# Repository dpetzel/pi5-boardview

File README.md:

# Raspberry Pi 5 board reconstruction

A KiCad 10 reconstruction of the Raspberry Pi 5 board (part placement, part identification, nets traced from the
real board), published as an interactive boardview for repair work.

> [!WARNING]
> **Unofficial, incomplete and possibly wrong.**
> * **Not official.** Not made, endorsed or checked by Raspberry Pi Ltd, and not based on official schematics or layout
>   files. "Raspberry Pi" is a trademark of Raspberry Pi Ltd; this project is not affiliated with it.
> * **Made by a hobbyist.** Reverse engineered by an untrained hobbyist from photos and multimeter probing, not by an
>   electronics professional.
> * **Incomplete and possibly wrong.** Many parts are unidentified and most nets are untraced. Positions, values, part
>   numbers and connections may be wrong, and your board revision may differ.
> * **Use at your own risk.** Board-level repair can destroy hardware and can be dangerous. Check everything against
>   your own board, your own measurements and the manufacturers' datasheets before you solder or apply power. Provided
>   "as is" with no warranty of any kind; the authors and contributors accept no liability for any damage or injury.

* **View it:** <https://dpetzel.github.io/pi5-boardview/>, rebuilt from `main` on every push
* **Download:** [`pi5-boardview.html`](https://dpetzel.github.io/pi5-boardview/pi5-boardview.html) (self-contained,
  works offline) and [`pi5.brd`](https://dpetzel.github.io/pi5-boardview/pi5.brd) (for
  [OpenBoardView](https://github.com/OpenBoardView/OpenBoardView)), always the latest build

## Repository

| Path | What |
|---|---|
| `pi5.kicad_pcb`, `pi5.kicad_pro` | The board. Top and bottom photos are embedded as reference images (Eco1.User = top, Eco2.User = bottom) |
| `pi5.pretty/`, `DA9091.pretty/` | Project footprints |
| `pi5_board_top.png`, `pi5_board_bottom.png` | The source photos embedded in the board |
| `tools/boardview.py`, `tools/template.html` | Exporter (HTML viewer + `.brd`) and the viewer it fills in |
| `.github/workflows/boardview.yml` | CI: builds the boardview and deploys it to Pages |

The boardview files are build output and not committed.

## Contributing

Edit the board in KiCad 10 and open a pull request. Part details go in footprint fields: `Function`, `Part`, `Notes`,
`Replacement`, and `Source` (`Source2`, `Source3`, … for more links). Fields holding a URL show as links in the
viewer. References ending in `**` or `?` (`REF**`, `R?`) are shown as unidentified parts.

Every pull request builds the boardview. Download the `boardview` artifact from the PR's workflow run to check
your change before it's merged.

### Building locally

The exporter needs KiCad's `pcbnew` Python module. With Docker:

```sh
docker run --rm -v "$PWD":/w -w /w kicad/kicad:10.0 python3 tools/boardview.py pi5.kicad_pcb
```

or with the Python bundled with KiCad (on Windows, `"C:\Program Files\KiCad\10.0\bin\python.exe"`):

```sh
python3 tools/boardview.py pi5.kicad_pcb
```

Both write `boardview/pi5-boardview.html` and `boardview/pi5.brd`. Options: `-o DIR`, `--no-photo`,
`--kicad-nets-only` (skip nets derived from copper; see the notes at the top of `tools/boardview.py`).
KiCad exports the last *saved* board, so save before building.

## Credits

The DA9091 PMIC footprint (`DA9091.pretty`, U5) uses the pad geometry from
[schlae/cm5-reveng](https://github.com/schlae/cm5-reveng), a reverse-engineered Raspberry Pi Compute Module 5,
licensed [CC BY-SA 4.0](https://creativecommons.org/licenses/by-sa/4.0/). Its pad numbers are left blank here on
purpose: the DA9091 has no public datasheet to confirm where pin 1 is.

## License

[CC-BY-SA-4.0](LICENSE): share and adapt with attribution, and publish adaptations under the same license.
The license's disclaimer of warranties and limitation of liability apply in full.

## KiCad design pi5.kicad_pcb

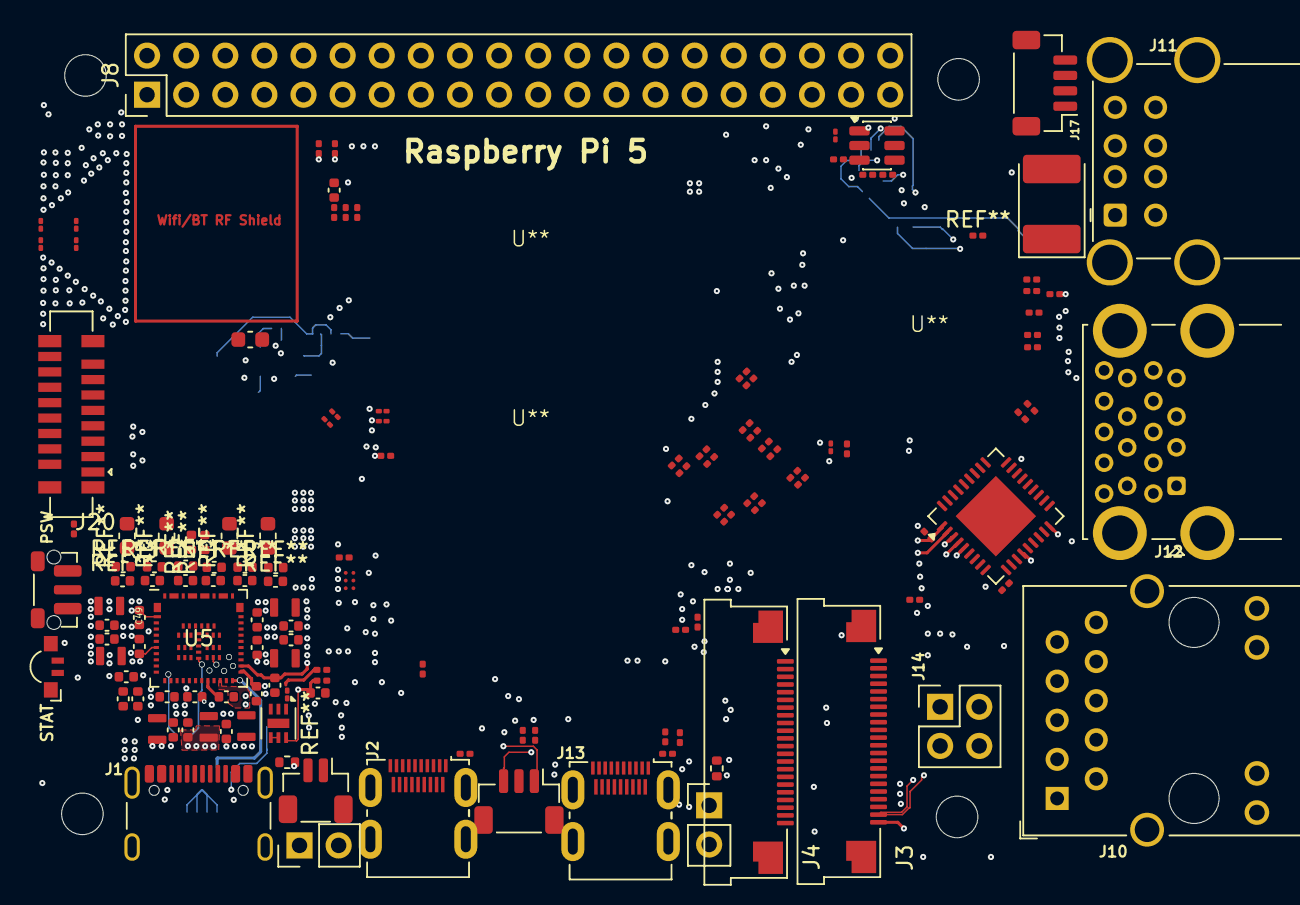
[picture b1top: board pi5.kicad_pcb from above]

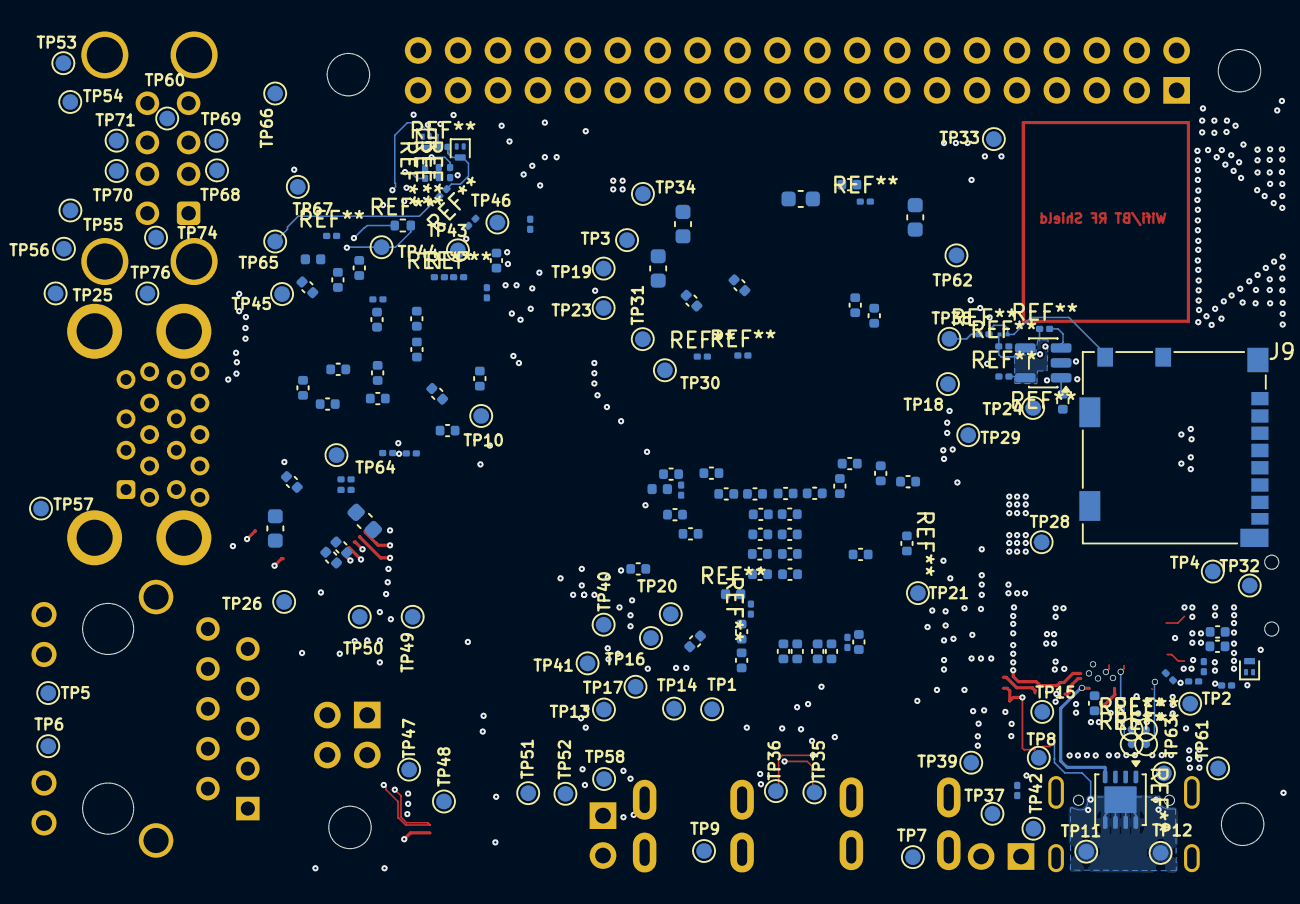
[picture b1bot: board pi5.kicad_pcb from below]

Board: 2 copper layers, 98 parts (78 on the bottom side), 4 nets.

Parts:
C49, C50: 22uF; C_0402_1005Metric
C234: 22uF; C_0603_1608Metric
C263: 4u7; C_0402_1005Metric
J1: USB_C_Receptacle_GCT_USB4105-xx-A_16P_TopMnt_Hori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; USB_C_Receptacle_GCT_USB4105-xx-A_16P_TopMnt_Horizontal
J2, J13: HDMI_Micro-D_Molex_46765-1xxx
J3, J4: F32Q-1A7H1-11022; Amphenol_F32Q-1A7x1-11022_1x22-1MP_P0.5mm_Horizontal
J8: PinHeader_2x20_P2.54mm_Vertical
J9: 104031-0811; microSD_HC_Molex_104031-0811
J10: RJ45_Wuerth_7499111446_Horizontal
J11: USB_A_Wuerth_61400826021_Horizontal_Stacked
J12: USB3_A_Molex_48406-0001_Horizontal_Stacked
J14: PinHeader_2x02_P2.54mm_Vertical
J17: JST_SH_BM04B-SRSS-TB_1x04-1MP_P1.00mm_Vertical
J20: 52559-1652; Molex_52559-1652_2x8-1MP_P0.5mm_Vertical
PSW: SW_Push_1P1T-MP_NO_Horizontal_Alps_SKRTLAE010
R15, R17: 470 Ω; R_0201_0603Metric
R46, R47: 2K Ω; R_0201_0603Metric
R93: 10K Ω; R_0201_0603Metric
STAT: LED_Kingbright_APFA3010_3x1.5mm_Horizontal
TP1, TP2, TP3, TP4, TP5, TP6, TP7, TP8, TP9, TP10, TP11, TP12, TP13, TP14, TP15, TP16, TP17, TP18, TP19, TP20, TP21, TP23, TP24, TP25, TP26, TP28, TP29, TP30, TP31, TP32, TP33, TP34, TP35, TP36, TP37, TP38, TP39, TP40, TP41, TP42, TP43, TP44, TP45, TP46, TP47, TP48, TP49, TP50, TP51, TP52, TP53, TP54, TP55, TP56, TP57, TP58, TP60, TP61, TP62, TP63, TP64, TP65, TP66, TP67, TP68, TP69, TP70, TP71, TP74, TP76: TestPoint_Pad_D1.0mm
U5: DA9091
U**: RP1-C0
U**#2: BCM2712
U**#3: LPDDR4X_SDRAM

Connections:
+5v: C49.2, C50.1, J8.2, J8.4
+5v_USB-C: TP11.1, TP12.1
GND: C49.1, C50.2, J8.6
SD_SW_DETECT: J9.9, J9.10, TP38.1

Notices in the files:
parts and their libraries:
DA9091 PMIC (QFN-71, 6x6 mm, 0.4 mm pitch). Pad geometry from U5 in schlae/cm5-reveng (https://github.com/schlae/cm5-reveng), CC BY-SA 4.0; pad numbers left blank on purpose: no public datasheet to confirm pin 1
